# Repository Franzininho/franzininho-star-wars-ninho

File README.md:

# franzininho-star-wars-ninho
Robô pisca com a temática Star Wars idealizado pelo [Professor Isidro](https://github.com/professorisidro).

As placas foram desenvolvidas usando Kicad 4.0.

A Pinagem dos shields são compatíveis apenas com [Franzininho](http://github.com/franzininho).

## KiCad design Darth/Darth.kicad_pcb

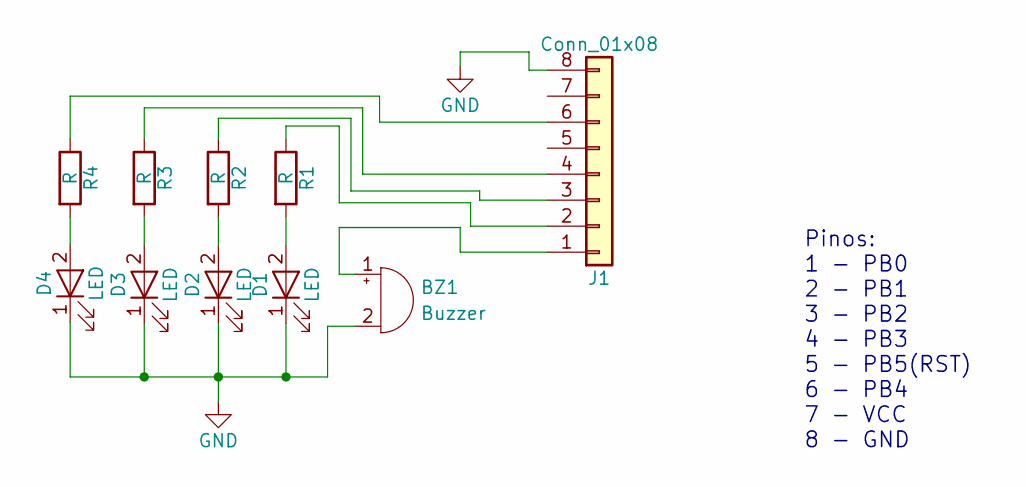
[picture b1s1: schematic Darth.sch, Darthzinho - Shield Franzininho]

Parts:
BZ1: Buzzer; Buzzer_12x9.5RM7.6
D1, D4: LED; LED_D3.0mm
D2, D3: LED; LED_D5.0mm
J1: Conn_01x08; Pin_Header_Angled_1x08_Pitch2.54mm
R1, R2, R3, R4: R; R_Axial_DIN0207_L6.3mm_D2.5mm_P7.62mm_Horizontal

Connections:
GND: BZ1.2 (+), D1.1 (K), D2.1 (K), D3.1 (K), D4.1 (K), J1.8
unnamed: BZ1.1 (-), J1.1
unnamed: D1.2 (A), R1.2
unnamed: D2.2 (A), R2.2
unnamed: D3.2 (A), R3.2
unnamed: D4.2 (A), R4.2
unnamed: J1.2, R1.1
unnamed: J1.3, R2.1
unnamed: J1.4, R3.1
unnamed: J1.6, R4.1

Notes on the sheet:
Pinos: 1 - PB0 2 - PB1 3 - PB2 4 - PB3 5 - PB5(RST) 6 - PB4 7 - VCC 8 - GND

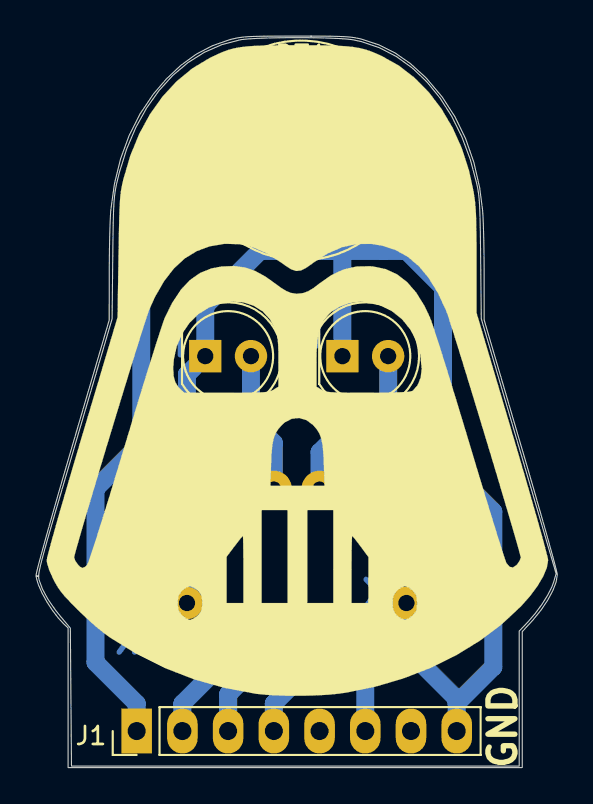
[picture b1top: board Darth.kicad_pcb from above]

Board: 2 copper layers, 29.0 x 40.6 mm, 11 parts (0 on the bottom side), 10 nets.

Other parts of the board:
Darthzinho: Darthzinho; darth_borda

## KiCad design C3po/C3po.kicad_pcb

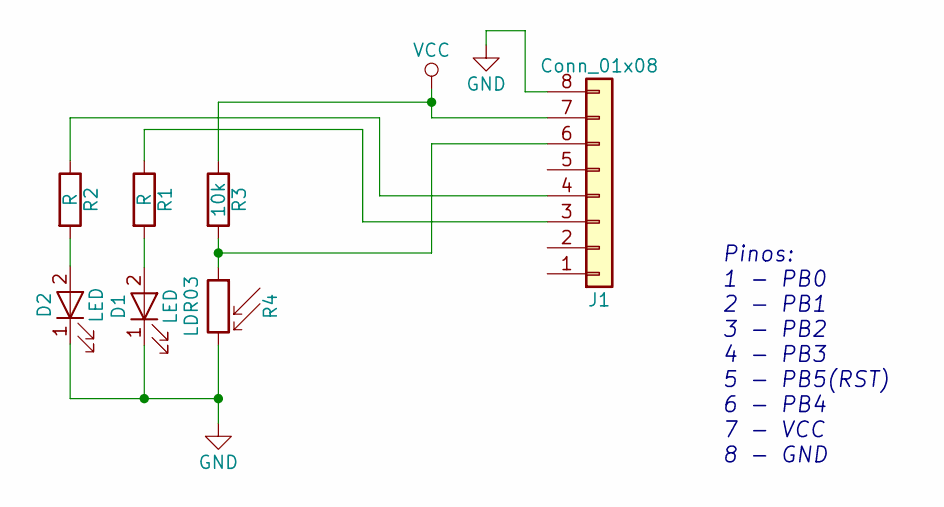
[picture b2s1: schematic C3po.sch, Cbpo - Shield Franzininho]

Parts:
D1, D2: LED; LED_D5.0mm
J1: Conn_01x08; Pin_Header_Straight_1x08_Pitch2.54mm
R1, R2: R; R_Axial_DIN0207_L6.3mm_D2.5mm_P7.62mm_Horizontal
R3: 10k; R_Axial_DIN0207_L6.3mm_D2.5mm_P7.62mm_Horizontal
R4: LDR03; Resistor_LDR_10x8.5_RM7.6

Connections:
GND: D1.1 (K), D2.1 (K), J1.8, R4.2
unnamed: D1.2 (A), R1.2
unnamed: D2.2 (A), R2.2
unnamed: J1.3, R1.1
unnamed: J1.4, R2.1
unnamed: J1.6, R3.2, R4.1
VCC: J1.7, R3.1

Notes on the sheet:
Pinos: 1 - PB0 2 - PB1 3 - PB2 4 - PB3 5 - PB5(RST) 6 - PB4 7 - VCC 8 - GND

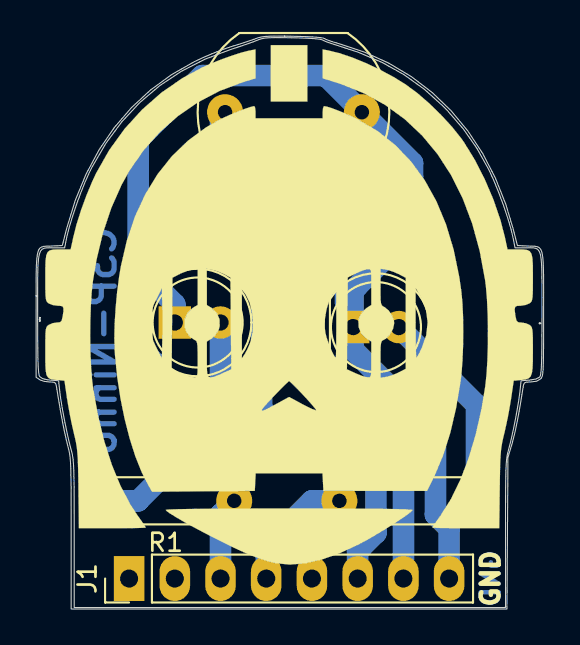
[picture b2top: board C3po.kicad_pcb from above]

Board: 2 copper layers, 28.2 x 31.8 mm, 8 parts (0 on the bottom side), 7 nets.

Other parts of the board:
C3P-Ninho: C3P-Ninho; C3po_borda

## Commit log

2018-03-18 atualizado Readme
2018-03-25 Versão inicial do protótipo
2018-03-25 Alerta da pinagem
